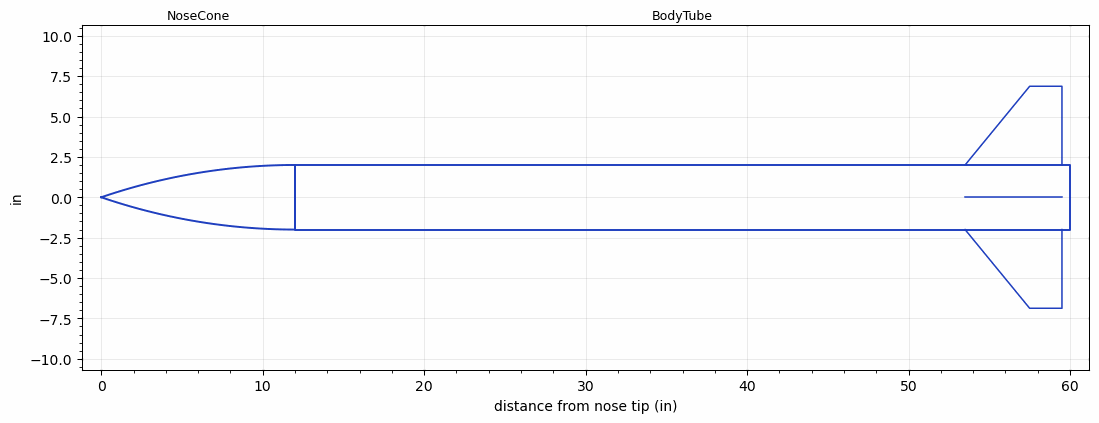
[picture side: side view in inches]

<RASAeroDocument>
 <FileVersion>2</FileVersion>
 <RocketDesign>
  <NoseCone>
   <Length>12</Length>
   <Diameter>4</Diameter>
   <Shape>Tangent Ogive</Shape>
   <Location>0</Location>
  </NoseCone>
  <BodyTube>
   <Length>47.9999</Length>
   <Diameter>4</Diameter>
   <Location>12</Location>
   <Fin>
    <Count>4</Count>
    <Chord>6</Chord>
    <Span>4.875</Span>
    <SweepDistance>4</SweepDistance>
    <TipChord>2</TipChord>
    <Thickness>0.125</Thickness>
    <Location>6.5</Location>
    <AirfoilSection>Hexagonal Blunt Base</AirfoilSection>
    <FX1>0.25</FX1>
   </Fin>
  </BodyTube>
  <Surface>Smooth (Zero Roughness)</Surface>
  <ModifiedBarrowman>False</ModifiedBarrowman>
  <Turbulence>True</Turbulence>
  <UseBooster1>False</UseBooster1>
  <UseBooster2>False</UseBooster2>
  <Comments>Extended controlled aerodynamic study: Hbev-span4.875</Comments>
 </RocketDesign>
 <LaunchSite>
  <Altitude>0</Altitude>
  <Pressure>29.9214</Pressure>
  <RodAngle>0</RodAngle>
  <RodLength>6.5617</RodLength>
  <Temperature>59</Temperature>
  <WindSpeed>0</WindSpeed>
 </LaunchSite>
 <Recovery>
  <Altitude1>656.168</Altitude1>
  <Altitude2>0</Altitude2>
  <DeviceType1>Parachute</DeviceType1>
  <DeviceType2>None</DeviceType2>
  <Event1>True</Event1>
  <Event2>False</Event2>
  <Size1>24</Size1>
  <Size2>0</Size2>
  <EventType1>Apogee</EventType1>
  <EventType2>None</EventType2>
  <CD1>0.8</CD1>
  <CD2>0</CD2>
 </Recovery>
 <SimulationList>
  <Simulation>
   <SustainerEngine>I500T-14A  (AT)</SustainerEngine>
   <SustainerLaunchWt>14.5064</SustainerLaunchWt>
   <SustainerCG>34.7639</SustainerCG>
   <SustainerIgnitionDelay>0</SustainerIgnitionDelay>
   <Booster1SeparationDelay>0</Booster1SeparationDelay>
   <Booster1IgnitionDelay>0</Booster1IgnitionDelay>
   <IncludeBooster1>False</IncludeBooster1>
   <Booster2Delay>0</Booster2Delay>
   <IncludeBooster2>False</IncludeBooster2>
   <TimetoApogee>9.190115</TimetoApogee>
   <MaxAltitude>1235.54</MaxAltitude>
   <MaxVelocity>270.5551</MaxVelocity>
  </Simulation>
  <Simulation>
   <SustainerEngine>J570W  (AT)</SustainerEngine>
   <SustainerLaunchWt>15.1813</SustainerLaunchWt>
   <SustainerCG>35.261</SustainerCG>
   <SustainerIgnitionDelay>0</SustainerIgnitionDelay>
   <Booster1SeparationDelay>0</Booster1SeparationDelay>
   <Booster1IgnitionDelay>0</Booster1IgnitionDelay>
   <IncludeBooster1>False</IncludeBooster1>
   <Booster2Delay>0</Booster2Delay>
   <IncludeBooster2>False</IncludeBooster2>
   <TimetoApogee>13.66022</TimetoApogee>
   <MaxAltitude>2940.604</MaxAltitude>
   <MaxVelocity>432.8058</MaxVelocity>
  </Simulation>
 </SimulationList>
</RASAeroDocument>
